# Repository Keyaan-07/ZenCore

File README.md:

# Zencore F4
Zencore F4 is a low-cost, Pico sized STM32F411 Development board along with an SD card reader for SDMMC development. The footprint is breadboard compatible and it features the W25Q128JVS 128Mbit Flash chip for non-volatile storage. Unlike traditional devboards, this features a compact form factor. The pins are labelled on the bottom side of the PCB.  
I want to use the stm32f411 mcu for a bigger project and thus i will be experimenting with this one(hence the SD card interface). Just plug in the USB-C to your PC and upload the code via STM32cubeIDE to get started.  
To build this, clone/download this repository, and in the /hardware/production folder, use the files and the bom to order the parts yourself and assemble it by hand!

See the board on [KiCanvas](https://kicanvas.org/?github=https://github.com/Keyaan-07/ZenCore/tree/main/hardware)

# BOM
|Designator              |Function         |Value                      |Footprint                                      |Quantity|Price        |Amount|Order|Link                                              |
|------------------------|-----------------|---------------------------|-----------------------------------------------|--------|-------------|------|-----|--------------------------------------------------|
|PCB                     |PCB              |21x51                      |2 layer board                                  |5       |0.42         |2.1   |Yes  |https://jlcpcb.com                                |
|PCB Stencil             |Stencil          |40x55                      |stencil                                        |1       |3.05         |3.05  |Yes  |https://jlcpcb.com                                |
|C1, C10, C12, C2, C3, C4|Capacitor        |100n                       |402                                            |12      |0.0075       |0.09  |No   |https://www.lcsc.com/product-detail/C426067.html  |
|C11                     |Capacitor        |10u                        |603                                            |2       |0.02         |0.04  |No   |https://www.lcsc.com/product-detail/C7393892.html |
|C5                      |Capacitor        |1u                         |402                                            |20      |0.03         |0.6   |yes  |https://www.lcsc.com/product-detail/C1518208.html |
|C6                      |Capacitor        |4.7u                       |402                                            |10      |0.04         |0.4   |Yes  |https://www.lcsc.com/product-detail/C426094.html  |
|C7, C8                  |Capacitor        |22p                        |402                                            |4       |0.03         |0.12  |No   |https://www.lcsc.com/product-detail/C882567.html  |
|C9                      |Capacitor        |22u                        |603                                            |10      |0.014        |0.14  |Yes  |https://www.lcsc.com/product-detail/C86295.html   |
|D1, D2                  |LED              |LED                        |402                                            |50      |0.01         |0.5   |Yes  |https://www.lcsc.com/product-detail/C7496805.html |
|J1                      |SD card connector|Micro_SD_Card              |microSD_HC_Molex_104031-0811                   |2       |0.63         |1.26  |Yes  |https://www.lcsc.com/product-detail/C585350.html  |
|J2                      |USB-C Receptacle |USB_C_Receptacle_USB2.0_16P|USB_C_Receptacle_XKB_U262-16XN-4BVC11          |10      |0.066        |0.66  |Yes  |https://www.lcsc.com/product-detail/C393939.html  |
|J3, J4                  |header           |Conn_01x20_Pin             |PinHeader_1x20_P2.54mm_Vertical                |2       |DNP          |DNP   |DNP  |DNP                                               |
|L1                      |Inductor         |2.2u                       |805                                            |5       |0.1          |0.5   |Yes  |https://www.lcsc.com/product-detail/C48945029.html|
|R1, R2, R3, R7, R9      |Resistors        |5.1k                       |402                                            |10      |0.005        |0.05  |No   |https://www.lcsc.com/product-detail/C278598.html  |
|R10, R4                 |Resistors        |100k                       |402                                            |4       |0.02         |0.08  |No   |https://www.lcsc.com/product-detail/C313329.html  |
|R5, R6                  |Resistors        |100R                       |402                                            |4       |0.037        |0.148 |No   |https://www.lcsc.com/product-detail/C427204.html  |
|SW1, SW2                |Switch           |SW_Push                    |SW-SMD_L3.9-W3.0-P4.45                         |10      |0.056        |0.56  |Yes  |https://www.lcsc.com/product-detail/C720477.html  |
|U1                      |flash chip       |W25Q128JVS                 |SOIC-8_5.3x5.3mm_P1.27mm                       |2       |DNP          |DNP   |DNP  |DNP                                               |
|U2                      |MCU              |STM32F411CEUx              |QFN-48-1EP_7x7mm_P0.5mm_EP5.6x5.6mm            |2       |3.87         |7.74  |Yes  |https://www.lcsc.com/product-detail/C60420.html   |
|U3                      |Buck Convertor   |TPS62162DSG                |WSON-8-1EP_2x2mm_P0.5mm_EP0.9x1.6mm_ThermalVias|2       |0.86         |1.72  |Yes  |https://www.lcsc.com/product-detail/C40256.html   |
|Y1                      |Crystal          |25MHz                      |Crystal_SMD_3225-4Pin_3.2x2.5mm                |2       |             |0     |No   |https://www.lcsc.com/product-detail/C521601.html  |
|                        |                 |                           |                                               |        |Shipping     |3.9   |     |                                                  |
|                        |                 |                           |                                               |        |Shipping(PCB)|11.13 |     |                                                  |
|                        |                 |                           |                                               |        |Total        |34.788|     |                                                  |

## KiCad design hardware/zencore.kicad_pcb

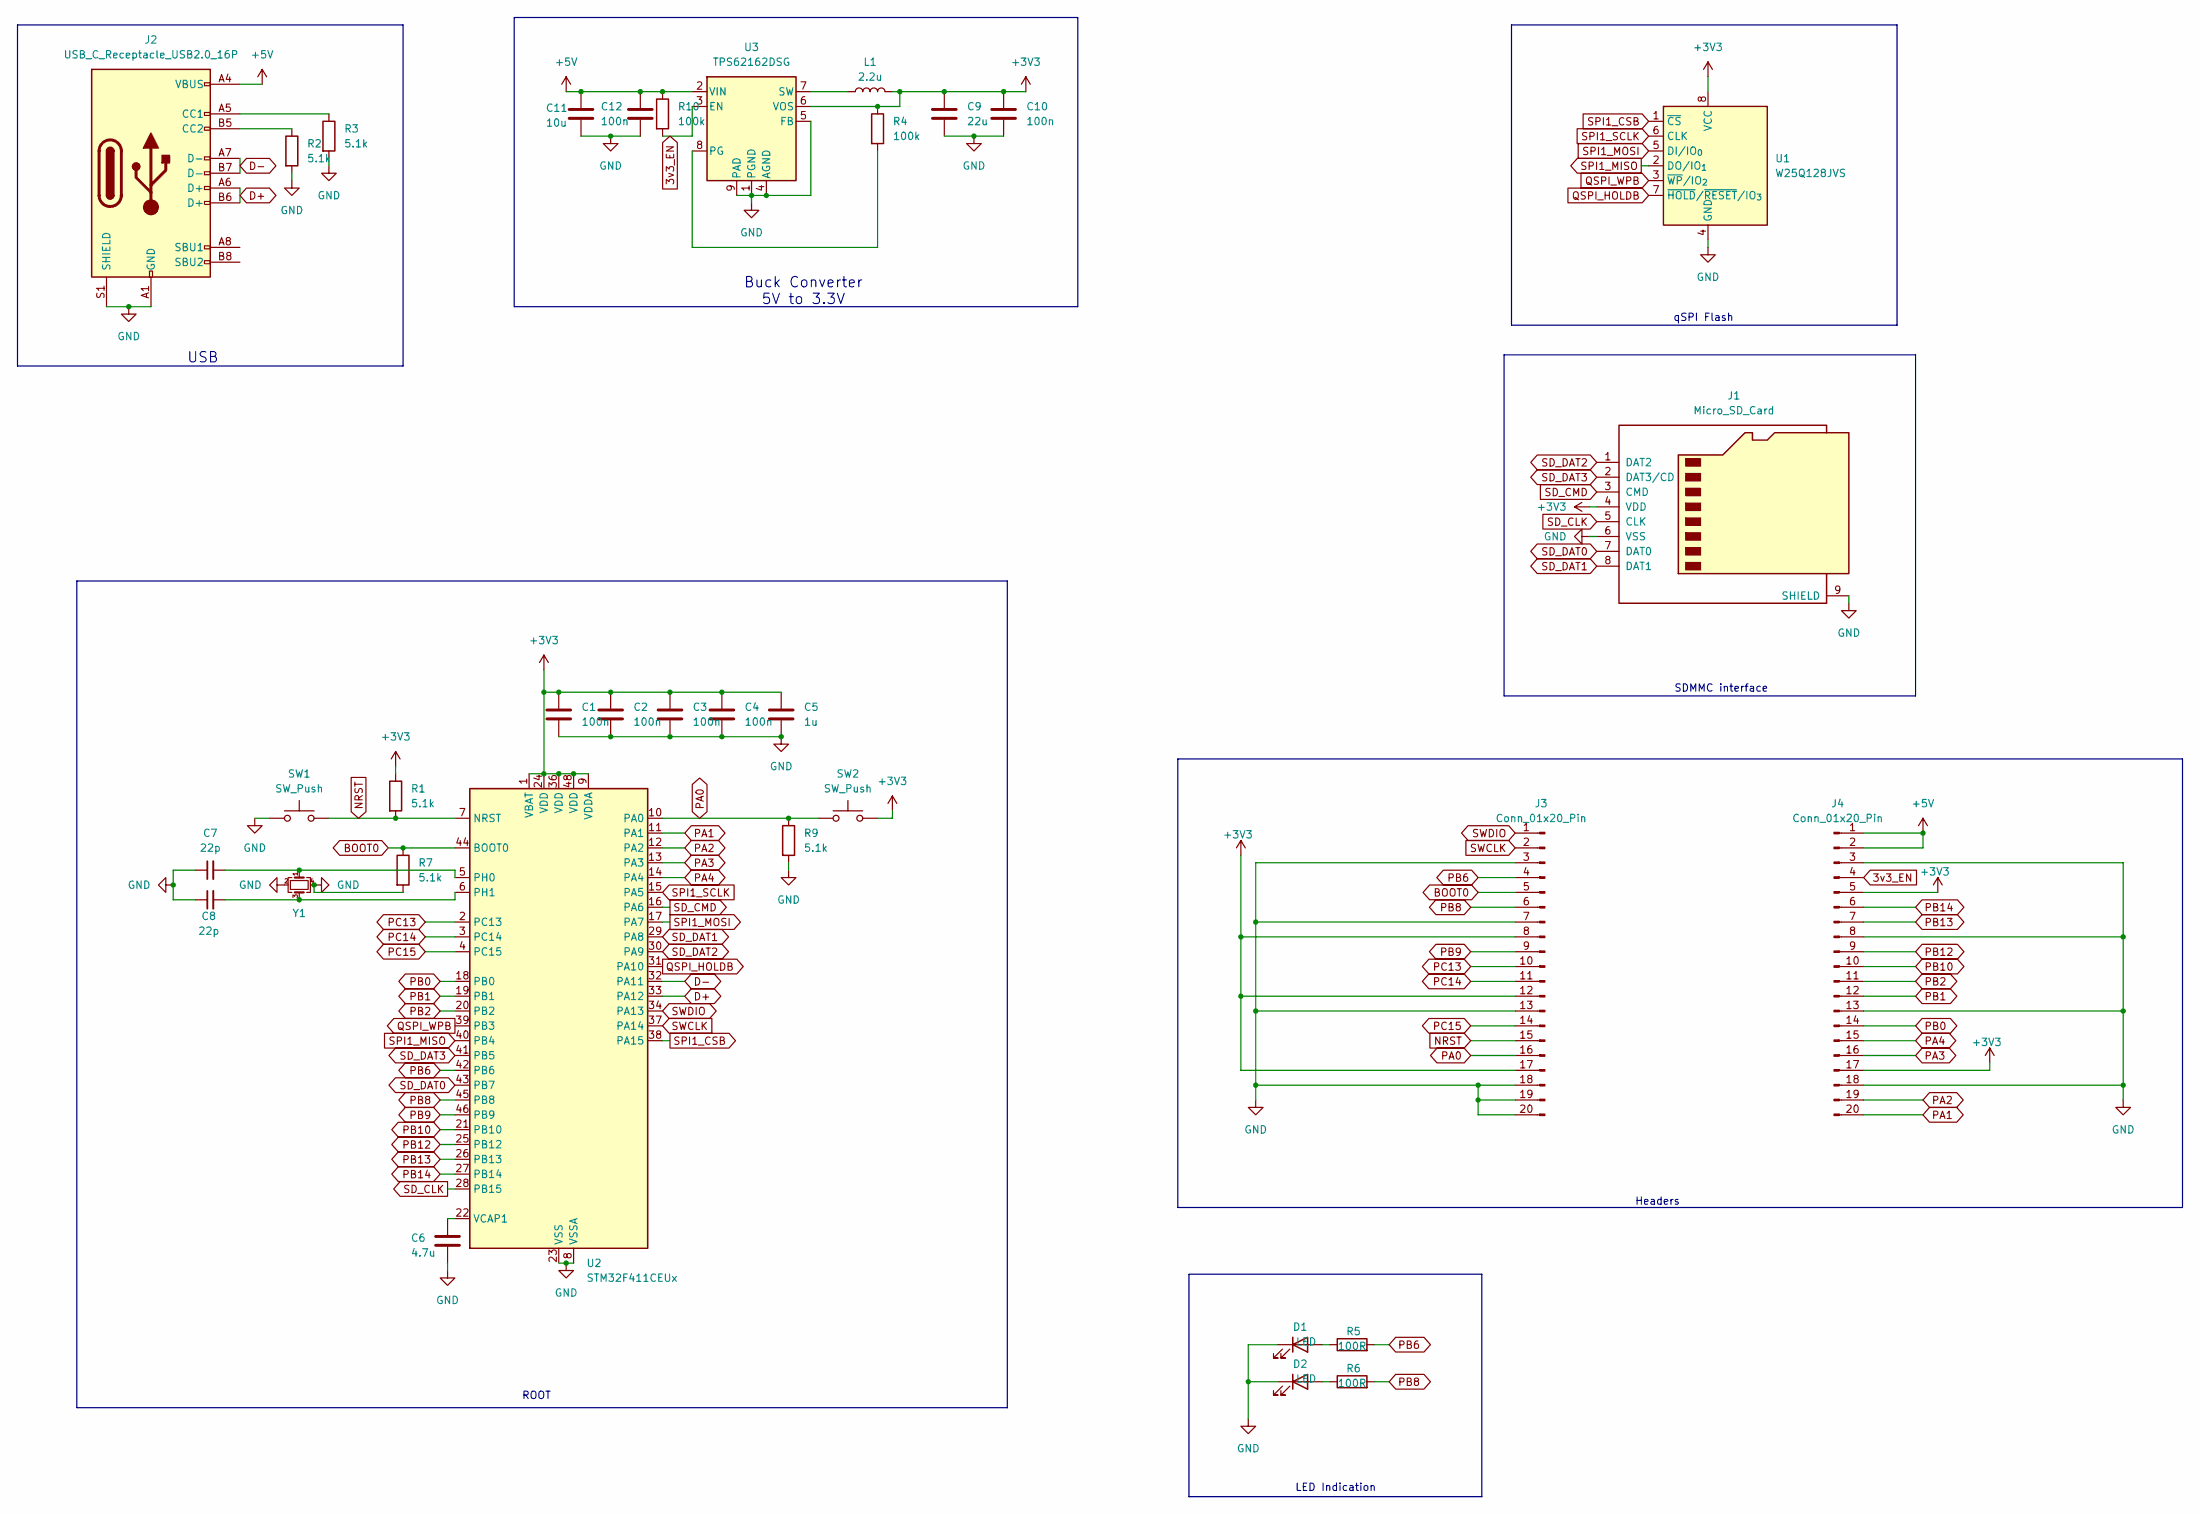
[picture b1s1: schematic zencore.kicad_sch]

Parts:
C1, C2, C3, C4, C10, C12: 100n; C_0402_1005Metric
C5: 1u; C_0402_1005Metric
C6: 4.7u; C_0402_1005Metric
C7, C8: 22p; C_0402_1005Metric
C9: 22u; C_0603_1608Metric
C11: 10u; C_0603_1608Metric
D1, D2: LED; LED_0402_1005Metric
J1: Micro_SD_Card; microSD_HC_Molex_104031-0811
J2: USB_C_Receptacle_USB2.0_16P; USB_C_Receptacle_XKB_U262-16XN-4BVC11
J3, J4: Conn_01x20_Pin; PinHeader_1x20_P2.54mm_Vertical
L1: 2.2u; L_0805_2012Metric
R1, R2, R3, R7, R9: 5.1k; R_0402_1005Metric
R4, R10: 100k; R_0402_1005Metric
R5, R6: 100R; R_0402_1005Metric
SW1, SW2: SW_Push; SW-SMD_L3.9-W3.0-P4.45
U1: W25Q128JVS; SOIC-8_5.3x5.3mm_P1.27mm
U2: STM32F411CEUx; QFN-48-1EP_7x7mm_P0.5mm_EP5.6x5.6mm
U3: TPS62162DSG; WSON-8-1EP_2x2mm_P0.5mm_EP0.9x1.6mm_ThermalVias
Y1: Crystal_GND24_Small; Crystal_SMD_3225-4Pin_3.2x2.5mm

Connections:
3v3_EN: J4.4, R10.2, U3.3 (EN)
+3V3: C1.1, C2.1, C3.1, C4.1, C5.1, C9.1, C10.1, J1.4 (VDD), J3.8, J3.12, J3.17, J4.5, J4.17, L1.2, R1.1, R4.1, SW2.2, U1.8 (VCC), U2.1 (VBAT), U2.9 (VDDA), U2.24 (VDD), U2.36 (VDD), U2.48 (VDD), U3.6 (VOS)
+5V: C11.1, C12.1, J2.A4 (VBUS), J2.A9 (VBUS), J2.B4 (VBUS), J2.B9 (VBUS), J4.1, J4.2, R10.1, U3.2 (VIN)
BOOT0: J3.5, R7.1, U2.44 (BOOT0)
D+: J2.A6 (D+), J2.B6 (D+), U2.33 (PA12)
D-: J2.A7 (D-), J2.B7 (D-), U2.32 (PA11)
GND: C1.2, C2.2, C3.2, C4.2, C5.2, C6.2, C7.1, C8.1, C9.2, C10.2, C11.2, C12.2, D1.1 (K), D2.1 (K), J1.6 (VSS), J1.9 (SHIELD), J2.A1 (GND), J2.A12 (GND), J2.B1 (GND), J2.B12 (GND), J2.S1 (SHIELD), J3.3, J3.7, J3.13, J3.18, J3.19, J3.20, J4.3, J4.8, J4.13, J4.18, R2.2, R3.2, R7.2, R9.2, SW1.1, U1.4 (GND), U2.8 (VSSA), U2.23 (VSS), U2.35 (VSS), U2.47 (VSS), U2.49 (VSS), U3.1 (PGND), U3.4 (AGND), U3.5 (FB), U3.9 (PAD), Y1.2, Y1.4
NRST: J3.15, R1.2, SW1.2, U2.7 (NRST)
unnamed: D1.2 (A), R5.1
unnamed: D2.2 (A), R6.1
unnamed: J2.A5 (CC1), R3.1
unnamed: J2.B5 (CC2), R2.1
unnamed: C7.2, U2.5 (PH0), Y1.1
unnamed: C8.2, U2.6 (PH1), Y1.3
unnamed: C6.1, U2.22 (VCAP1)
unnamed: R4.2, U3.8 (PG)
unnamed: L1.1, U3.7 (SW)
PA0: J3.16, R9.1, SW2.1, U2.10 (PA0)
PA1: J4.20, U2.11 (PA1)
PA2: J4.19, U2.12 (PA2)
PA3: J4.16, U2.13 (PA3)
PA4: J4.15, U2.14 (PA4)
PB0: J4.14, U2.18 (PB0)
PB1: J4.12, U2.19 (PB1)
PB2: J4.11, U2.20 (PB2)
PB6: J3.4, R5.2, U2.42 (PB6)
PB8: J3.6, R6.2, U2.45 (PB8)
PB9: J3.9, U2.46 (PB9)
PB10: J4.10, U2.21 (PB10)
PB12: J4.9, U2.25 (PB12)
PB13: J4.7, U2.26 (PB13)
PB14: J4.6, U2.27 (PB14)
PC13: J3.10, U2.2 (PC13)
PC14: J3.11, U2.3 (PC14)
PC15: J3.14, U2.4 (PC15)
QSPI_HOLDB: U1.7 (~HOLD/~RESET/IO_{3}), U2.31 (PA10)
QSPI_WPB: U1.3 (~WP/IO_{2}), U2.39 (PB3)
SD_CLK: J1.5 (CLK), U2.28 (PB15)
SD_CMD: J1.3 (CMD), U2.16 (PA6)
SD_DAT0: J1.7 (DAT0), U2.43 (PB7)
SD_DAT1: J1.8 (DAT1), U2.29 (PA8)
SD_DAT2: J1.1 (DAT2), U2.30 (PA9)
SD_DAT3: J1.2 (DAT3/CD), U2.41 (PB5)
SPI1_CSB: U1.1 (~CS), U2.38 (PA15)
SPI1_MISO: U1.2 (DO/IO_{1}), U2.40 (PB4)
SPI1_MOSI: U1.5 (DI/IO_{0}), U2.17 (PA7)
SPI1_SCLK: U1.6 (CLK), U2.15 (PA5)
SWCLK: J3.2, U2.37 (PA14)
SWDIO: J3.1, U2.34 (PA13)

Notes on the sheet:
LED Indication
SDMMC interface
ROOT
Headers
qSPI Flash
USB
Buck Converter 5V to 3.3V

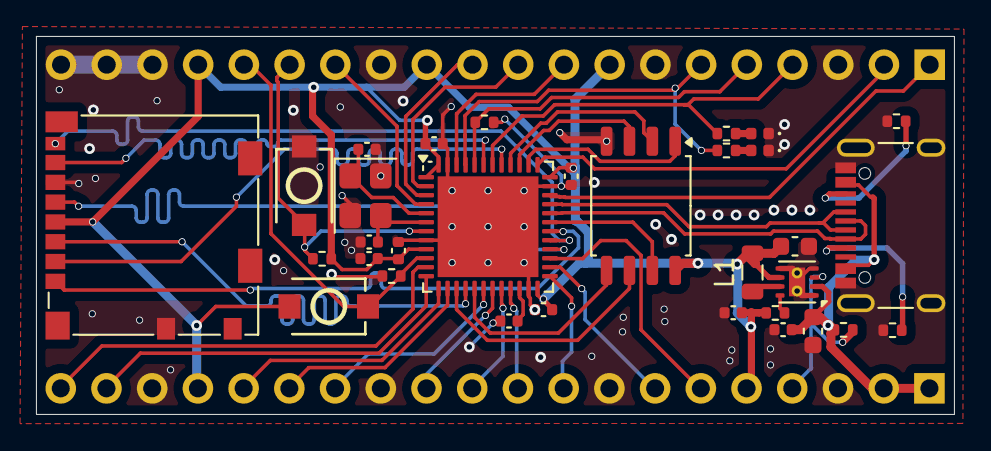
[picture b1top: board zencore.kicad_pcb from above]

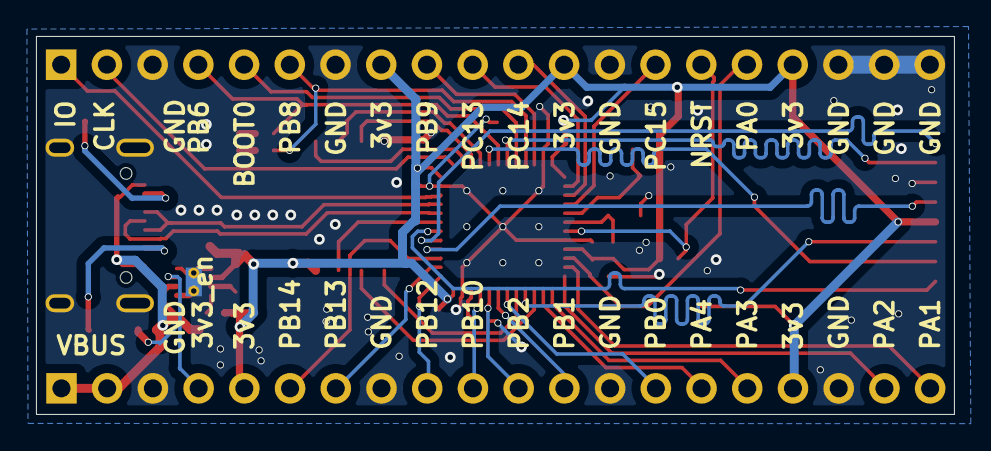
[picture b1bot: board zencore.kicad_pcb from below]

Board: 2 copper layers, 51.0 x 21.0 mm, 34 parts (2 on the bottom side), 49 nets.

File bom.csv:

Designator,Function,Value,Footprint,Quantity,Price,Amount,Order,Link
PCB,PCB,21x51,2 layer board,5,0.42,2.1,Yes,https://jlcpcb.com
PCB Stencil,Stencil,40x55,stencil,1,3.05,3.05,Yes,https://jlcpcb.com
"C1, C10, C12, C2, C3, C4",Capacitor,100n,402,12,0.0075,0.09,No,https://www.lcsc.com/product-detail/C426067.html
C11,Capacitor,10u,603,2,0.02,0.04,No,https://www.lcsc.com/product-detail/C7393892.html
C5,Capacitor,1u,402,20,0.03,0.6,yes,https://www.lcsc.com/product-detail/C1518208.html
C6,Capacitor,4.7u,402,10,0.04,0.4,Yes,https://www.lcsc.com/product-detail/C426094.html
"C7, C8",Capacitor,22p,402,4,0.03,0.12,No,https://www.lcsc.com/product-detail/C882567.html
C9,Capacitor,22u,603,10,0.014,0.14,Yes,https://www.lcsc.com/product-detail/C86295.html
"D1, D2",LED,LED,402,50,0.01,0.5,Yes,https://www.lcsc.com/product-detail/C7496805.html
J1,SD card connector,Micro_SD_Card,microSD_HC_Molex_104031-0811,2,0.63,1.26,Yes,https://www.lcsc.com/product-detail/C585350.html
J2,USB-C Receptacle,USB_C_Receptacle_USB2.0_16P,USB_C_Receptacle_XKB_U262-16XN-4BVC11,10,0.066,0.66,Yes,https://www.lcsc.com/product-detail/C393939.html
"J3, J4",header,Conn_01x20_Pin,PinHeader_1x20_P2.54mm_Vertical,2,DNP,DNP,DNP,DNP
L1,Inductor,2.2u,805,5,0.1,0.5,Yes,https://www.lcsc.com/product-detail/C48945029.html
"R1, R2, R3, R7, R9",Resistors,5.1k,402,10,0.005,0.05,No,https://www.lcsc.com/product-detail/C278598.html
"R10, R4",Resistors,100k,402,4,0.02,0.08,No,https://www.lcsc.com/product-detail/C313329.html
"R5, R6",Resistors,100R,402,4,0.037,0.148,No,https://www.lcsc.com/product-detail/C427204.html
"SW1, SW2",Switch,SW_Push,SW-SMD_L3.9-W3.0-P4.45,10,0.056,0.56,Yes,https://www.lcsc.com/product-detail/C720477.html
U1,flash chip,W25Q128JVS,SOIC-8_5.3x5.3mm_P1.27mm,2,DNP,DNP,DNP,DNP
U2,MCU,STM32F411CEUx,QFN-48-1EP_7x7mm_P0.5mm_EP5.6x5.6mm,2,3.87,7.74,Yes,https://www.lcsc.com/product-detail/C60420.html
U3,Buck Convertor,TPS62162DSG,WSON-8-1EP_2x2mm_P0.5mm_EP0.9x1.6mm_ThermalVias,2,0.86,1.72,Yes,https://www.lcsc.com/product-detail/C40256.html
Y1,Crystal,25MHz,Crystal_SMD_3225-4Pin_3.2x2.5mm,2,,0,No,https://www.lcsc.com/product-detail/C521601.html
,,,,,Shipping,3.9,,
,,,,,Shipping(PCB),11.13,,
,,,,,Total,34.788,,

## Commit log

2026-03-12 Hello, World
2026-03-12 ADD README
2026-03-18 Worked on the schematic
2026-04-17 Routing done
2026-05-04 3D models added
2026-05-06 PCB production files added
2026-05-06 Introductory paragraph
2026-05-06 Added PCB and 3D model images
2026-05-06 3D model file uploaded
2026-05-06 Final modifications and file generation
2026-05-06 Upload BOM
2026-05-06 Update BOM
2026-05-07 added magazine page
2026-05-07 print quality magazine page
2026-05-07 Add LICENSE
2026-05-07 Build info
2026-05-07 pdf file name change
